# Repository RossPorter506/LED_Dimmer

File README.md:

# LED_Dimmer
Schematic and PCB layout for a dumb 5-12V LED dimming circuit, capable of 2-99% PWM-based dimming.

No MCUs, no intelligent internet-connected devices, just a good old fashioned analog PWM dimmer using a 555 timer and a potentiometer.

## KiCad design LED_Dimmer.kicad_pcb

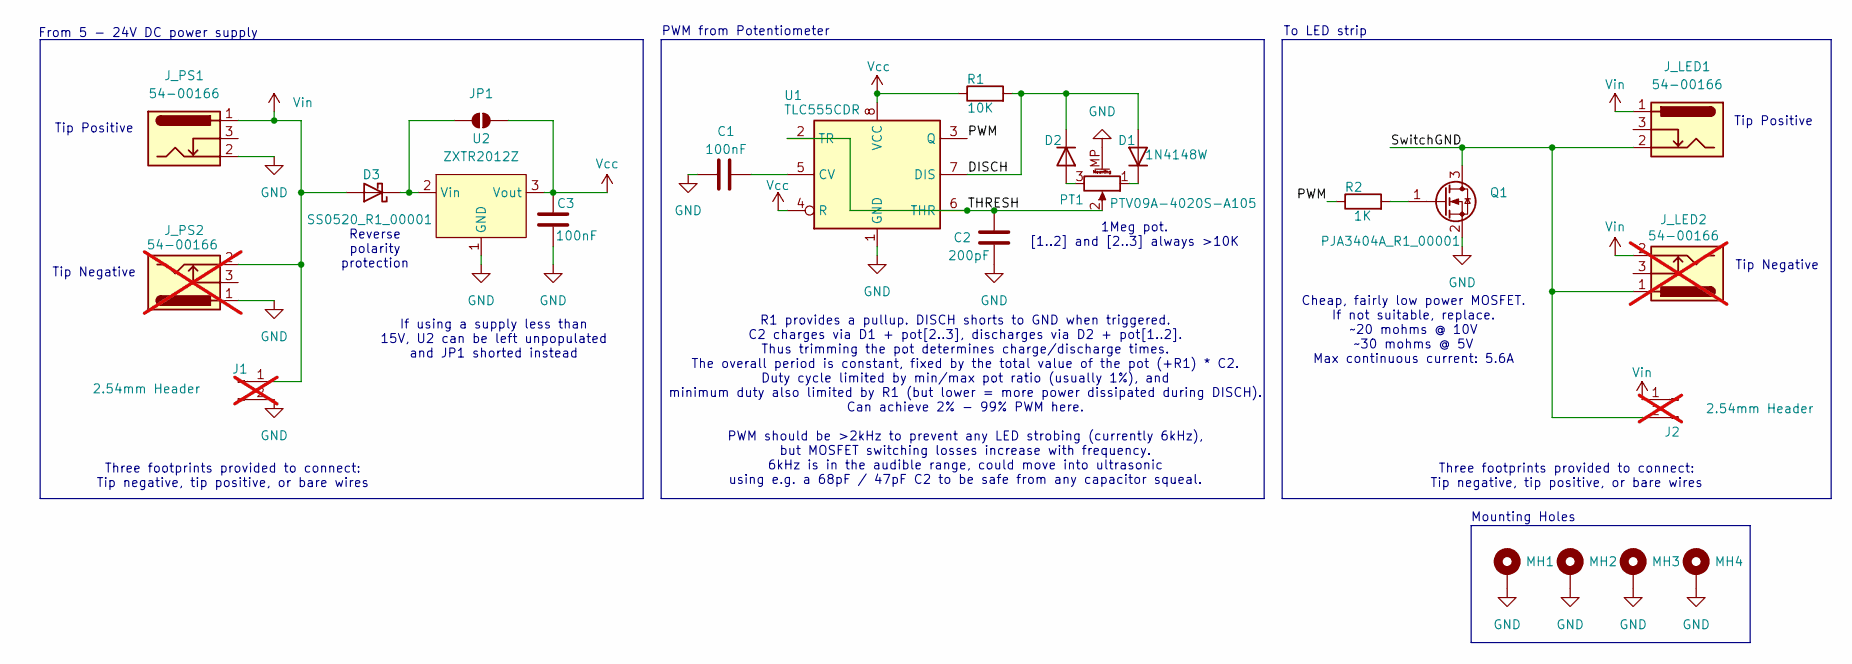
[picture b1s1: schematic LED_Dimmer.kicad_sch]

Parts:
C1, C3: 100nF; C_0805_2012Metric_Pad1.18x1.45mm_HandSolder
C2: 200pF; C_0805_2012Metric_Pad1.18x1.45mm_HandSolder
D1, D2: 1N4148W; D_SOD-123
D3: SS0520_R1_00001; D_SOD-123
J1, J2: 2.54mm Header; PinHeader_1x02_P2.54mm_Vertical; not fitted
JP1: SolderJumper_2_Open; SolderJumper-2_P1.3mm_Open_RoundedPad1.0x1.5mm
J_LED1: 54-00166; BarrelJack_GCT_DCJ200-10-A_Horizontal
J_LED2: 54-00166; BarrelJack_GCT_DCJ200-10-A_Horizontal; not fitted
J_PS1: 54-00166; BarrelJack_GCT_DCJ200-10-A_Horizontal
J_PS2: 54-00166; BarrelJack_GCT_DCJ200-10-A_Horizontal; not fitted
MH1, MH2, MH3, MH4: MountingHole_Pad; MountingHole_2.2mm_M2_Pad
PT1: PTV09A-4020S-A105; Potentiometer_Bourns_PTV09A-1_Single_Vertical
Q1: PJA3404A_R1_00001; SOT-23-3
R1: 10K; R_0805_2012Metric_Pad1.20x1.40mm_HandSolder
R2: 1K; R_0805_2012Metric_Pad1.20x1.40mm_HandSolder
U1: TLC555CDR; SOIC-8_3.9x4.9mm_P1.27mm
U2: ZXTR2012Z; SOT-89-3

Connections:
/DISCH: D1.2 (A), D2.1 (K), R1.2, U1.7 (DIS)
/PWM: R2.1, U1.3 (Q)
/SwitchGND: J2.2, J_LED1.2, J_LED2.1, Q1.3 (D)
/THRESH: C2.1, PT1.2, U1.2 (TR), U1.6 (THR)
GND: C1.1, C2.2, C3.1, J1.2, J_PS1.2, J_PS2.1, MH1.1, MH2.1, MH3.1, MH4.1, PT1.MP (MountPin), Q1.2 (S), U1.1 (GND), U2.1 (GND)
unnamed: D1.1 (K), PT1.1
unnamed: D2.2 (A), PT1.3
unnamed: D3.1 (K), JP1.1 (A), U2.2 (Vin)
unnamed: Q1.1 (G), R2.2
unnamed: C1.2, U1.5 (CV)
Vcc: C3.2, JP1.2 (B), R1.1, U1.4 (R), U1.8 (VCC), U2.3 (Vout)
Vin: D3.2 (A), J1.1, J2.1, J_LED1.1, J_LED2.2, J_PS1.1, J_PS2.2

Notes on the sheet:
Tip Positive
From 5 - 24V DC power supply
Tip Negative
To LED strip
If using a supply less than 15V, U2 can be left unpopulated and JP1 shorted instead
R1 provides a pullup. DISCH shorts to GND when triggered. C2 charges via D1 + pot[2..3], discharges via D2 + pot[1..2]. Thus trimming the pot determines charge/discharge times. The overall period is constant, fixed by the total value of the pot (+R1) * C2. Duty cycle limited by min/max pot ratio (u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
PWM from Potentiometer
Cheap, fairly low power MOSFET. If not suitable, replace. ~20 mohms @ 10V ~30 mohms @ 5V Max continuous current: 5.6A
Three footprints provided to connect: Tip negative, tip positive, or bare wires
1Meg pot. [1..2] and [2..3] always >10K
Reverse polarity protection
Mounting Holes

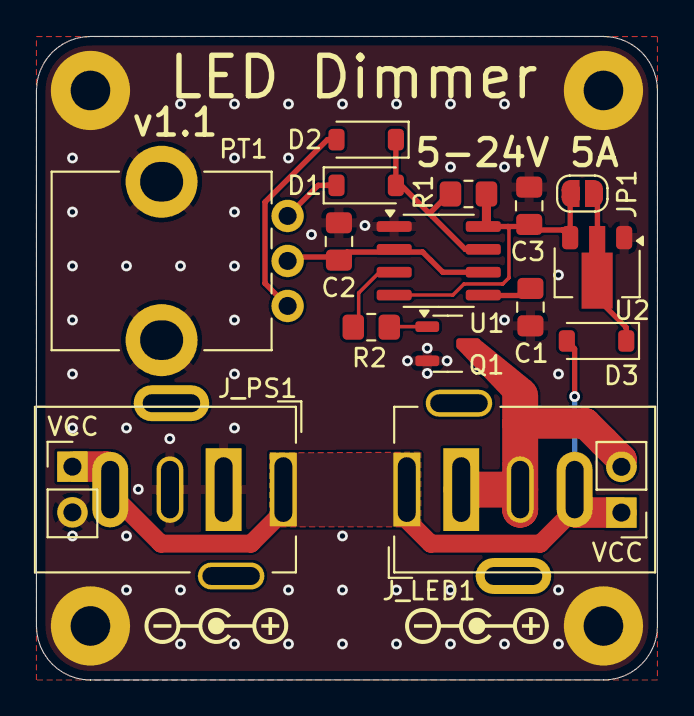
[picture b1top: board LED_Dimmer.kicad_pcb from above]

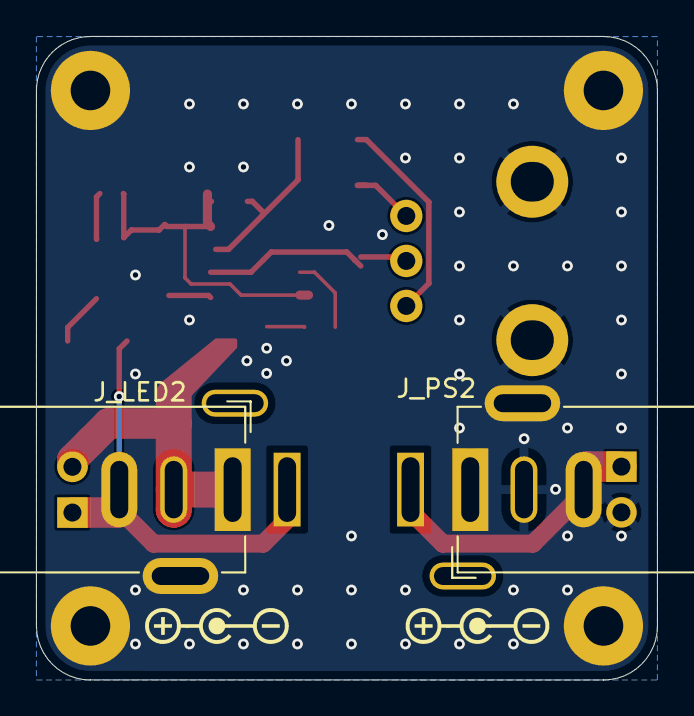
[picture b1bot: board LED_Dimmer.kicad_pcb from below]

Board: 2 copper layers, 34.5 x 35.8 mm, 27 parts (4 on the bottom side), 12 nets.

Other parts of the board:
G1_F, G1_F#2, G1_R, G2_R: LOGO

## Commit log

2025-07-14 Start work
2025-07-15 Add polarity images, pot footprint, tidy PCB
    Should work for 5V LEDs too, so change project name
2025-07-15 Add Schottky part number
2025-07-15 Tidy schematic, add serial number location to PCB
2025-07-15 Add Gerbers
2025-07-15 Rename project
2025-07-15 Fix diode part number
2025-08-21 Add current limiting resistor to FET
2025-08-21 Add optional regulator for 24V LEDs
2025-08-21 Update simulation with TLC555
2025-08-21 Fix MOSFET pin order
